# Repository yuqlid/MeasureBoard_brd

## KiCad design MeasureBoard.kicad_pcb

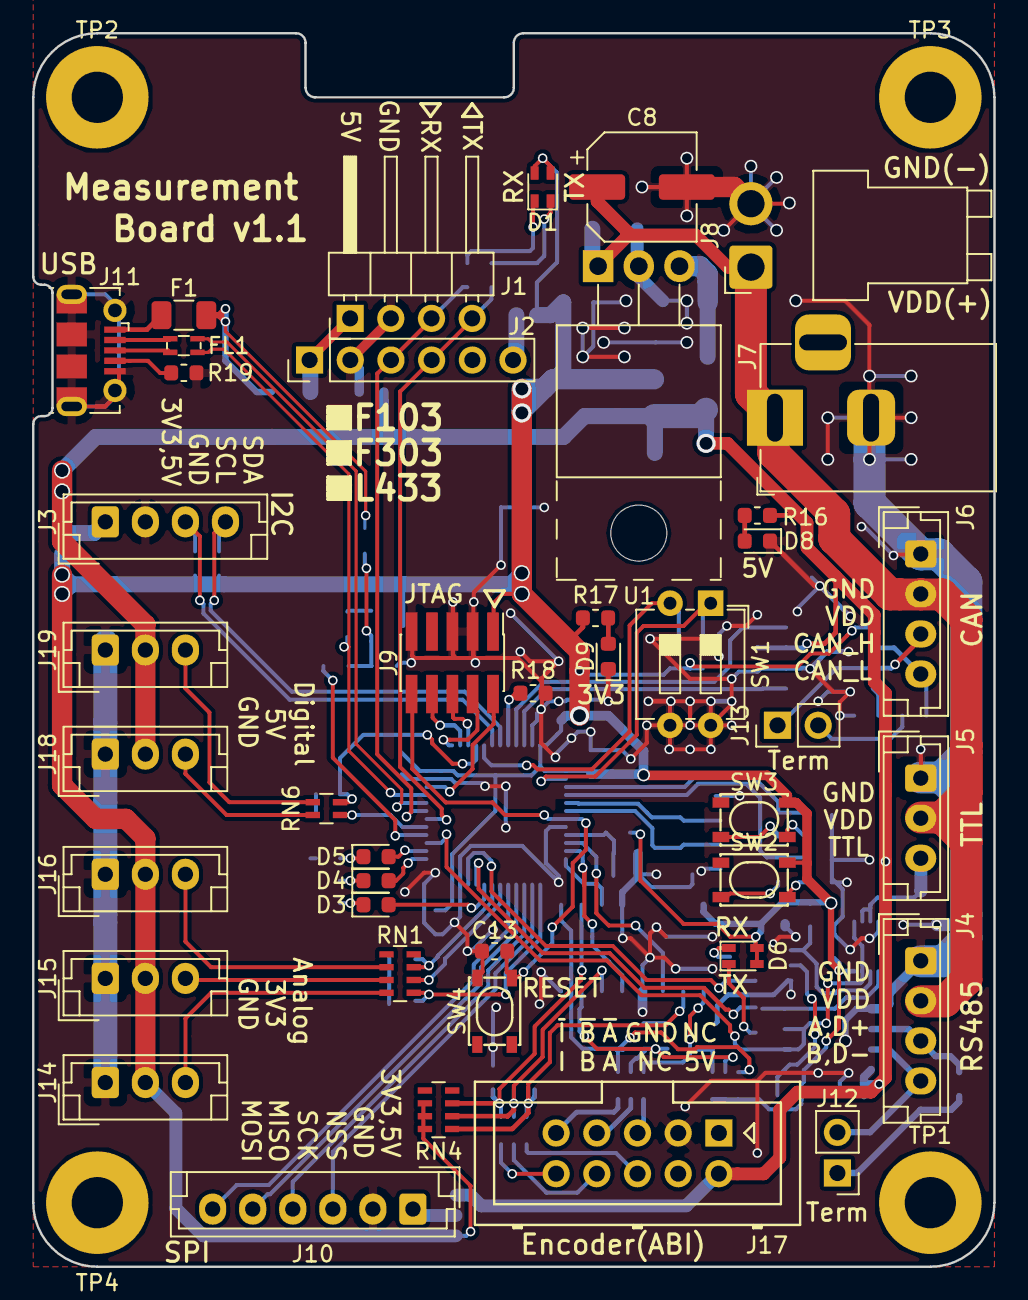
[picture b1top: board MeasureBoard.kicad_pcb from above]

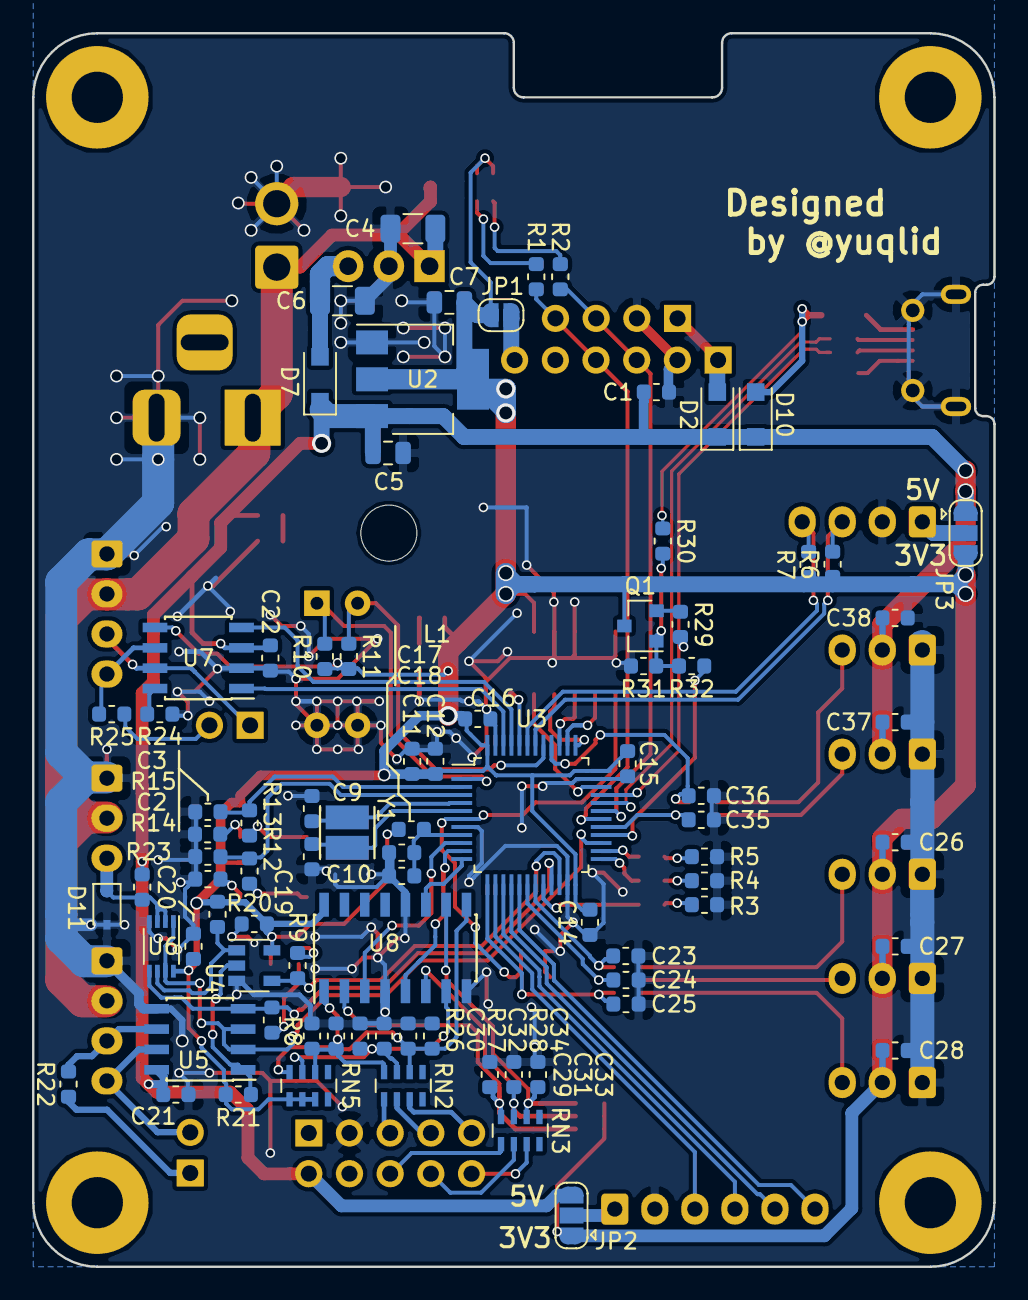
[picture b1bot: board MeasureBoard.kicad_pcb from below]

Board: 2 copper layers, 60.0 x 77.0 mm, 130 parts (84 on the bottom side), 96 nets.

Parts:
C1, C12, C13, C14, C15, C16, C18, C19, C20, C21, C22, C26, C27, C28, C37, C38: 0.1u; C_0603_1608Metric
C2, C3: C; C_0603_1608Metric
C4, C6: C; C_1206_3216Metric
C5, C7: C; C_0805_2012Metric
C8: CP; CP_Elec_6.3x9.9
C9, C10: 14p; C_0603_1608Metric
C11, C17: 1u; C_0603_1608Metric
C23, C24, C25: 1n; C_0603_1608Metric
C29, C30, C31, C32, C33, C34, C35, C36: 220p; C_0603_1608Metric
D1, D6: LED_Dual_ACAC; LED_STANLEY_1211C
D2, D7, D10: D; D_SOD-123F
D3, D4, D5, D8, D9: LED; LED_0603_1608Metric
D11: D_TVS; D_SOD-323
F1: Fuse; Fuse_1206_3216Metric
FL1: EMI_Filter_CommonMode; L_Murata_DLW21HN900SQ2#
J1: Conn_01x04; PinHeader_1x04_P2.54mm_Horizontal
J2: Conn_01x06; PinHeader_1x06_P2.54mm_Vertical
J3, J4, J6: Conn_01x04; JST_EH_B04B-EH-A_1x04_P2.50mm_Vertical
J5, J14, J15, J16, J18, J19: Conn_01x03; JST_EH_B03B-EH-A_1x03_P2.50mm_Vertical
J7: Barrel_Jack_Switch; BarrelJack_Horizontal
J8: Conn_01x02; JST_VH_B2PS-VH_1x02_P3.96mm_Horizontal
J9: Conn_02x05_Odd_Even; PinHeader_2x05_P1.27mm_Vertical_SMD
J10: Conn_01x06; JST_EH_B06B-EH-A_1x06_P2.50mm_Vertical
J11: USB_B_Micro; USB_Micro-B_Molex-105017-0001
J12, J13: Conn_01x02; PinHeader_1x02_P2.54mm_Vertical
J17: Conn_02x05_Odd_Even; Multicomp_MC9A12-1034_2x05_P2.54mm_Vertical
JP1: Jumper_2_Open; SolderJumper-2_P1.3mm_Open_RoundedPad1.0x1.5mm
JP2: SolderJumper_3_Open; SolderJumper-3_P1.3mm_Open_RoundedPad1.0x1.5mm
JP3: Jumper_NC_Dual; SolderJumper-3_P1.3mm_Open_RoundedPad1.0x1.5mm
L1: L; L_0603_1608Metric
Q1: BSS138; SOT-23
R1, R2, R3, R4, R5, R8, R9, R16, R17: 1k; R_0603_1608Metric
R6, R7, R10, R11, R12, R13: 4k7; R_0603_1608Metric
R14, R15, R18, R20, R21, R23, R30: 10k; R_0603_1608Metric
R19, R24, R32: R; R_0603_1608Metric
R22, R25: 120; R_0603_1608Metric
R26, R27, R28: 20k; R_0603_1608Metric
R29: 1.5k; R_0603_1608Metric
R31: 36k; R_0603_1608Metric
RN1, RN2, RN3, RN4, RN5: R_Pack04; R_Array_Concave_4x0603
RN6: R_Pack02; R_Array_Concave_2x0603
SW1: DIP_SW_2P; SW_DIP_SPSTx02_Slide_6.7x6.64mm_W7.62mm_P2.54mm_LowProfile
SW2, SW3, SW4: SKRPACE010; ALPS_SKRPAxE010
TP1, TP2, TP3, TP4: TestPoint; MountingHole_3.2mm_M3_Pad
U1: L7805; TO-220-3_Horizontal_TabUp
U2: AP1117-33; SOT-223-3_TabPin2
U3: STM32F303CCTx; LQFP-48_7x7mm_P0.5mm
U4: NC7SZ08; SOT-23-5
U5: SP3481CN; SOIC-8_3.9x4.9mm_P1.27mm
U6: NC7WZ241; VSSOP-8_2.3x2mm_P0.5mm
U7: MCP2562-E-SN; SOIC-8_3.9x4.9mm_P1.27mm
U8: AM26LV32; SOIC-16_3.9x9.9mm_P1.27mm
Y1: Crystal; NDK_Crystal_SMD_3225_2Pads

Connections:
+3V3: C7.1, C11.2, C12.1, C14.2, C15.2, C16.2, C19.1, C20.1, C26.1, C27.1, C28.1, D1.1, D1.3, D6.1, D6.3, J9.1, J14.2, J15.2, J16.2, JP1.2, JP2.1, JP3.3, L1.1, Q1.3, R6.1, R7.1, R10.1, R11.1, R17.1, R20.1, R21.1, RN4.6, RN4.7, RN4.8, RN5.5, RN5.6, RN5.7, SW2.2, SW3.2, U2.2, U3.1, U3.24, U3.36, U3.48, U4.5, U6.8, U7.5, U8.16
+5V: C1.1, C5.1, C21.1, C22.1, C37.1, C38.1, D2.1, D7.1, D10.1, J17.2, J18.2, J19.2, JP2.3, JP3.1, R16.1, R23.1, U2.3, U5.8, U7.3
+12V: C4.1, C8.1, J4.2, J5.2, J6.2, J7.1, J8.1, U1.1
/CAN/CAN_H: J6.3, J13.1, U7.7
/CAN/CAN_L: J6.4, R25.2, U7.6
/ENCODER/A: U3.10, U8.3
/ENCODER/B: U3.11, U8.5
/ENCODER/I: U3.12, U8.11
/IN_Di/DI1_LPF: C36.1, RN6.2, U3.40
/IN_Di/DI2_LPF: C35.1, RN6.1, U3.29
/JTAG/SWCLK-TCK: J9.4, U3.37
/JTAG/SWDIO-TMS: J9.2, U3.34
/JTAG/SWO-TDO: J9.6, U3.39
/MCU/ADC_IN3: C25.1, RN1.1, U3.13
/MCU/ADC_IN8: C24.1, RN1.2, U3.18
/MCU/ADC_IN9: C23.1, RN1.3, U3.19
/MCU/CAN_RX: U3.45, U7.4
/MCU/CAN_TX: U3.46, U7.1
/MCU/I2C1_SCL: J3.3, R6.2, U3.42
/MCU/I2C1_SDA: J3.4, R7.2, U3.43
/MCU/PB2: D3.2, U3.20
/MCU/PB5: R11.2, SW1.2, U3.41
/MCU/PB12: D4.2, U3.25
/MCU/PB13: D5.2, U3.26
/MCU/PC13: R10.2, SW1.1, U3.2
/MCU/PC14: C3.2, R13.2, U3.3
/MCU/PC15: C2.2, R12.2, U3.4
/MCU/SYS_JTDI: J9.8, U3.38
/MCU/USART1_RX: J1.3, J2.3, R2.1, U3.31
/MCU/USART1_TX: J1.4, J2.4, R1.1, U3.30
/MCU/USART3_RTS: U3.27, U5.2, U5.3, U6.1, U6.7
/RS485-TTL/DI: R8.1, U3.21, U5.4, U6.5
/RS485-TTL/RO: R9.1, U3.22, U4.4
/RS485-TTL/RS485_A: J4.3, R22.2, U5.6
/RS485-TTL/RS485_B: J4.4, J12.2, U5.7
/RS485-TTL/TTL_DATA: D11.1, J5.3, R23.2, U6.2, U6.3
/SSI/DATA_MISO: J10.5, U3.16
/SSI/MOSI: J10.6, U3.17
/SSI/NSS: J10.3, U3.14
/SSI/SCK: J10.4, U3.15
/USB/D+: FL1.4, R29.2, U3.33
/USB/D-: FL1.2, U3.32
/USB/USB_+: FL1.3, J11.3
/USB/USB_-: FL1.1, J11.2
/USB_EN: R32.1, U3.28
GND: C1.2, C2.1, C3.1, C4.2, C5.2, C6.2, C7.2, C8.2, C9.2, C10.2, C11.1, C12.2, C13.2, C14.1, C15.1, C16.1, C17.1, C18.1, C19.2, C20.2, C21.2, C22.2, C23.2, C24.2, C25.2, C26.2, C27.2, C28.2, C29.2, C30.2, C31.2, C32.2, C33.2, C34.2, C35.2, C36.2, C37.2, C38.2, D8.1, D9.1, D11.2, J1.2, J2.2, J3.2, J4.1, J5.1, J6.1, J7.2, J8.2, J9.3, J9.5, J9.9, J10.2, J11.5, J11.6, J14.1, J15.1, J16.1, J17.3, J18.1, J19.1, R3.2, R4.2, R5.2, R14.1, R15.1, R18.2, R19.2, R24.2, R26.2, R27.2, R28.2, R31.2, SW1.3, SW1.4, SW4.2, U1.2, U2.1, U3.8, U3.23, U3.35, U3.47, U4.3, U5.5, U6.4, U7.2, U8.4, U8.8, U8.12
NRST: C13.1, J9.10, SW4.4, U3.7
unnamed: C6.1, D7.2, U1.3
unnamed: C9.1, U3.5, Y1.1
unnamed: C10.1, U3.6, Y1.2
unnamed: C17.2, C18.2, L1.2, U3.9
unnamed: C29.1, RN3.8, RN4.1, U8.2
unnamed: C30.1, R26.1, RN2.8, RN5.2, U8.1
unnamed: C31.1, RN3.7, RN4.2, U8.6
unnamed: C32.1, R27.1, RN2.7, RN5.3, U8.7
unnamed: C33.1, RN3.6, RN4.3, U8.10
unnamed: C34.1, R28.1, RN2.6, RN5.4, U8.9
unnamed: D1.2, R2.2
unnamed: D1.4, R1.2
unnamed: D2.2, J1.1, J2.1
unnamed: D3.1, R3.1
unnamed: D4.1, R4.1
unnamed: D5.1, R5.1
unnamed: D6.2, R9.2
unnamed: D6.4, R8.2
unnamed: D8.2, R16.2
unnamed: D9.2, R17.2
unnamed: D10.2, F1.1, R30.1
unnamed: F1.2, J11.1
unnamed: J2.6, JP1.1
unnamed: J3.1, JP3.2
unnamed: J10.1, JP2.2
unnamed: J11.4, R19.1
unnamed: J12.1, R22.1
unnamed: J13.2, R25.1
unnamed: J14.3, RN1.8
unnamed: J15.3, RN1.7
unnamed: J16.3, RN1.6
unnamed: J17.5, RN2.1
unnamed: J17.6, RN3.1
unnamed: J17.7, RN2.2
unnamed: J17.8, RN3.2
unnamed: J17.9, RN2.3
unnamed: J17.10, RN3.3
unnamed: J18.3, RN6.4
unnamed: J19.3, RN6.3
unnamed: Q1.1, R30.2, R31.1, R32.2
unnamed: Q1.2, R29.1
unnamed: R12.1, SW2.3
unnamed: R13.1, SW3.3
unnamed: R14.2, SW2.4
unnamed: R15.2, SW3.4
unnamed: R18.1, U3.44
unnamed: R20.2, U4.1, U6.6
unnamed: R21.2, U4.2, U5.1
unnamed: R24.1, U7.8

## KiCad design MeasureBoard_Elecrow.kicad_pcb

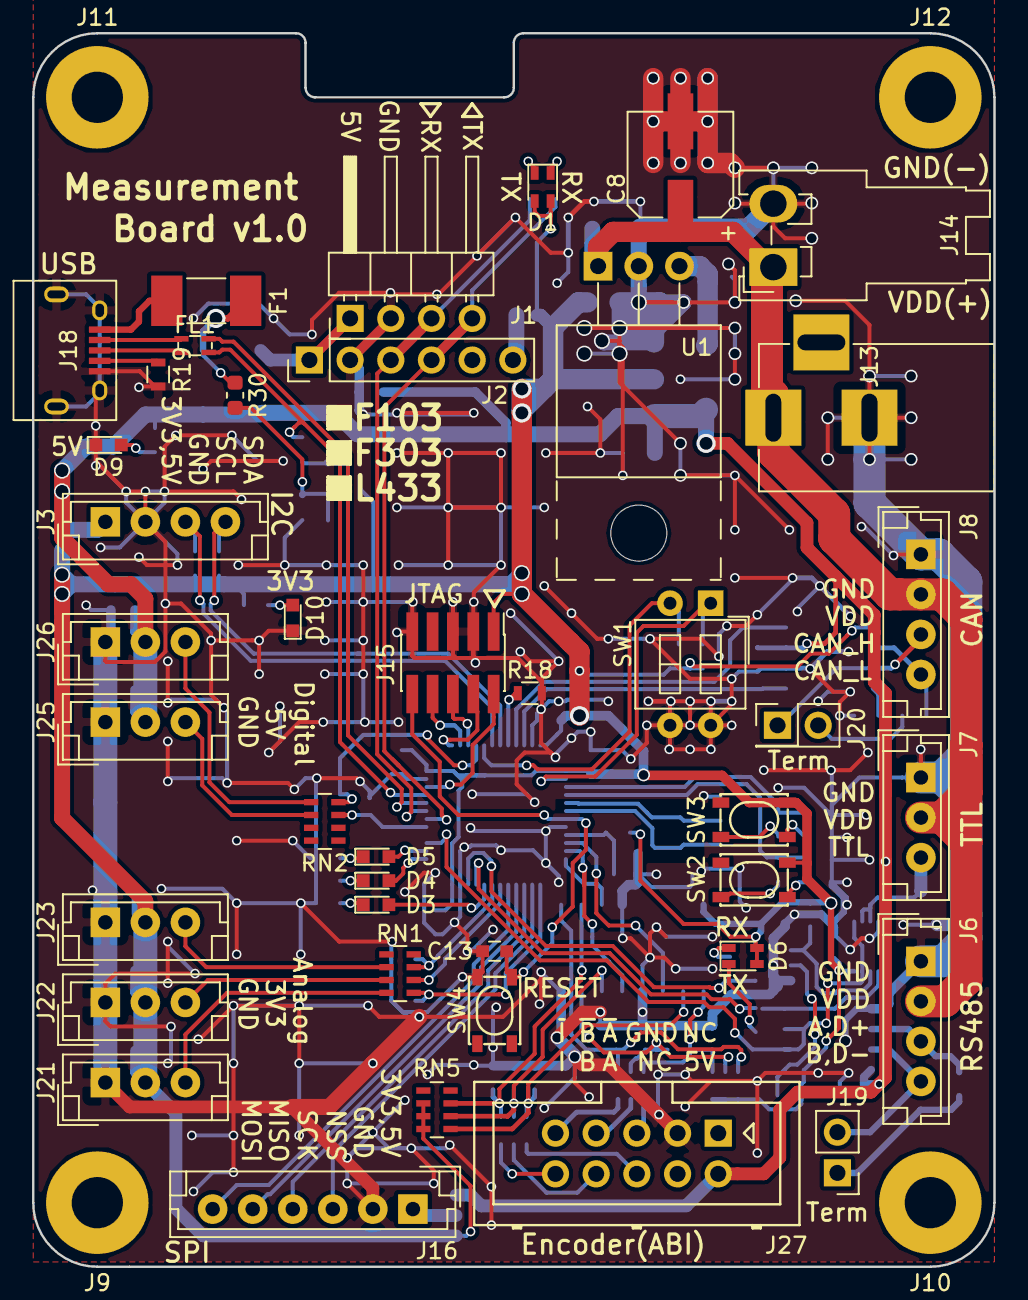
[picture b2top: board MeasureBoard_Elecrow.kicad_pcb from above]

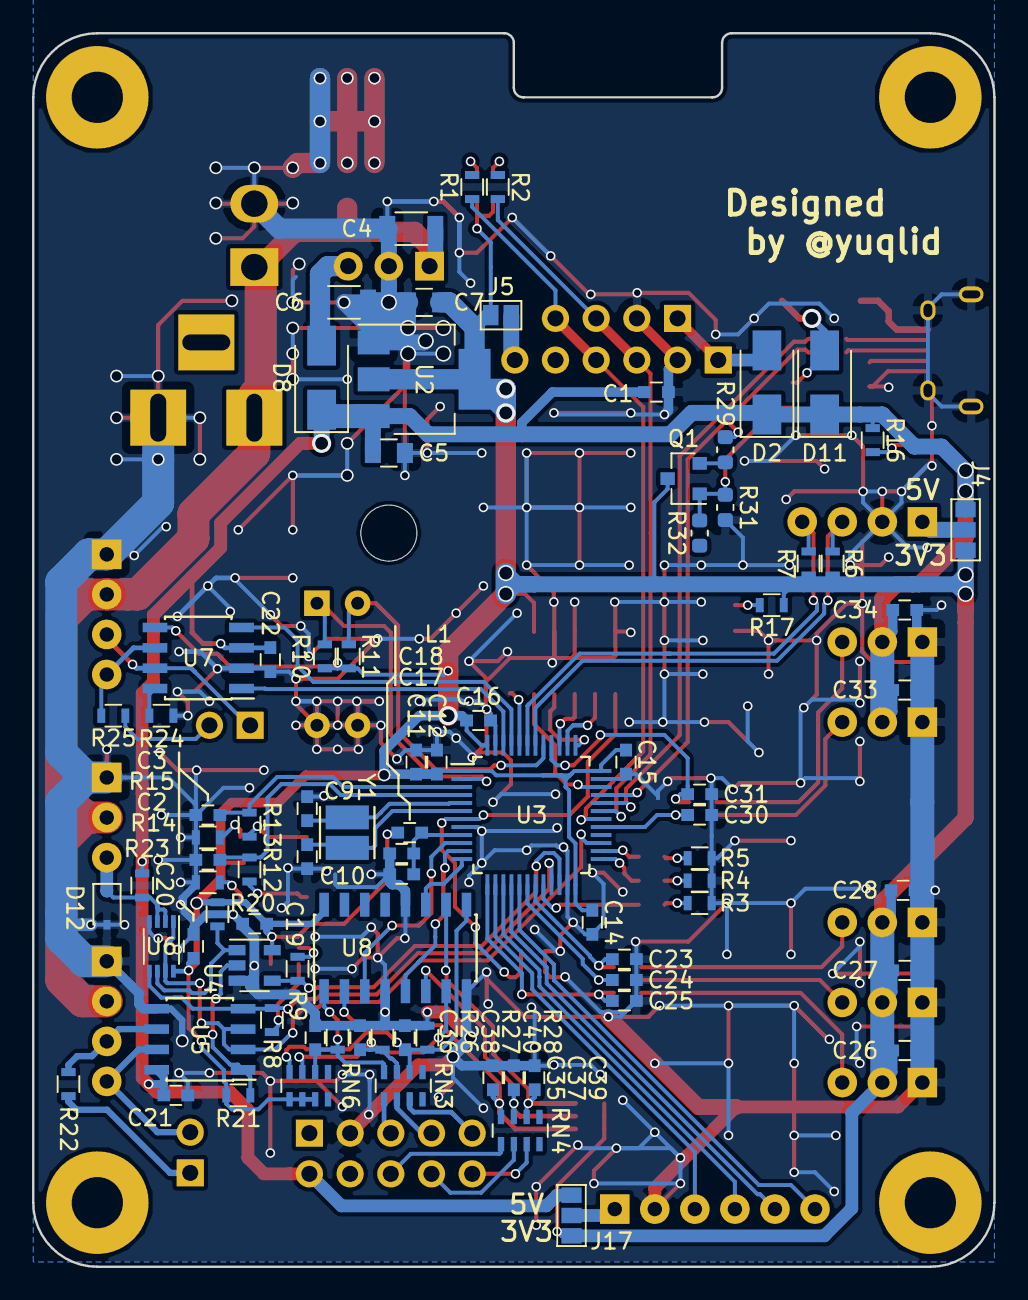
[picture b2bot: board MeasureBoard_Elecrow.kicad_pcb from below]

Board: 2 copper layers, 60.0 x 77.0 mm, 130 parts (85 on the bottom side), 96 nets.

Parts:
C1, C2, C3, C12, C13, C14, C15, C16, C18, C19, C20, C21, C22, C26, C27, C28, C33, C34: 0.1u; C_0603
C4, C6: C; C_1206
C5, C7: C; C_0805
C8: CP; CP_Elec_6.3x7.7
C9, C10: 14p; C_0603
C11, C17: 1u; C_0603
C23, C24, C25: 1n; C_0603
C30, C31, C35, C36, C37, C38, C39, C40: 220p; C_0603
D1, D6: LED_Dual_ACAC; LED_STANLEY_1211C
D2, D8, D11: D; D_SMA
D3, D4, D5, D9, D10: LED; LED_0603
D12: D_TVS; D_SOD-323
F1: Fuse; Fuse_0679H
FL1: EMI_Filter_CommonMode; L_Murata_DLW21HN900SQ2#
J1: Conn_01x04; Pin_Header_Angled_1x04_Pitch2.54mm
J2: Conn_01x06; Pin_Header_Straight_1x06_Pitch2.54mm
J3, J6, J8: Conn_01x04; JST_EH_B04B-EH-A_04x2.50mm_Straight
J4, J17: GS3
J5: GS2
J7, J21, J22, J23, J25, J26: Conn_01x03; JST_EH_B03B-EH-A_03x2.50mm_Straight
J9, J10, J11, J12: TEST_1P; MountingHole_3.2mm_M3_Pad
J13: BARREL_JACK
J14: CONN_01X02; JST_VH_S2P-VH_2x2x3.96mm_Horizontal
J15: Conn_02x05_Odd_Even; Pin_Header_Straight_2x05_Pitch1.27mm_SMD
J16: Conn_01x06; JST_EH_B06B-EH-A_06x2.50mm_Straight
J18: USB_OTG; USB_Micro-B
J19: Conn_01x02; Pin_Header_Straight_1x02_Pitch2.54mm
J20: Conn_01x02; Pin_Header_Straight_2x01_Pitch2.54mm
J27: Conn_02x05_Odd_Even; Multicomp_MC9A12-1034_2x05x2.54mm_Straight
L1: L; C_0603
Q1: BSS138; SOT-23
R1, R2, R3, R4, R5, R8, R9, R16, R17: 1k; R_0603
R6, R7, R10, R11, R12, R13: 4.7k; R_0603
R14, R15, R18, R20, R21, R23: 10k; R_0603
R19: 100k; R_0603
R22, R25: 120; R_0603
R24: R; R_0603
R26, R27, R28: 20k; R_0603
R29: 1.5k; R_0603_1608Metric
R30: 10k; R_0603_1608Metric
R31: 36k; R_0603_1608Metric
R32: R; R_0603_1608Metric
RN1, RN5: 10k_4; R_Array_Concave_4x0603
RN2, RN3, RN4: 150_4; R_Array_Concave_4x0603
RN6: 20k_4; R_Array_Concave_4x0603
SW1: DIP_SW_2P; SW_DIP_x2_W7.62mm_Slide_LowProfile
SW2, SW3, SW4: SKRPACE010; ALPS_SKRPAxE010
U1: L7805; TO-220-3_Horizontal_Reversed
U2: AP1117-33; SOT-223-3_TabPin2
U3: STM32F103CBTx; LQFP-48_7x7mm_Pitch0.5mm
U4: NC7SZ08; SOT-23-5
U5: SP3481CN; SOIC-8_3.9x4.9mm_Pitch1.27mm
U6: NC7WZ241; VSSOP-8_2.3x2mm_Pitch0.5mm
U7: MCP2562-E-SN; SOIC-8_3.9x4.9mm_Pitch1.27mm
U8: AM26LV32; SOIC-16_3.9x9.9mm_Pitch1.27mm
Y1: Crystal; NDK_Crystal_SMD_3225_2Pads

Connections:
+3V3: C7.1, C11.1, C12.1, C14.1, C15.1, C16.1, C19.1, C20.1, C26.1, C27.1, C28.1, D1.1, D1.3, D6.1, D6.3, J4.1, J5.1, J15.1, J17.1, J21.2, J22.2, J23.2, L1.1, Q1.3, R6.1, R7.1, R10.1, R11.1, R17.2, R20.2, R21.2, RN5.6, RN5.7, RN5.8, RN6.5, RN6.6, RN6.7, SW2.2, SW3.2, U2.2, U3.1, U3.24, U3.36, U3.48, U4.5, U6.8, U7.5, U8.16
+5V: C1.1, C5.1, C21.1, C22.1, C33.1, C34.1, D2.1, D8.1, D11.1, J4.3, J17.3, J25.2, J26.2, J27.2, R16.2, R23.2, U2.3, U5.8, U7.3
+12V: C4.1, C8.1, J6.2, J7.2, J8.2, J13.1, J14.1, U1.1
/CAN/CAN_H: J8.3, J20.1, U7.7
/CAN/CAN_L: J8.4, R25.1, U7.6
/ENCODER/A: U3.10, U8.3
/ENCODER/B: U3.11, U8.5
/ENCODER/I: U3.12, U8.11
/IN_Di/DI1_LPF: C31.1, RN2.4, U3.40
/IN_Di/DI2_LPF: C30.1, RN2.3, U3.29
/JTAG/SWCLK-TCK: J15.4, U3.37
/JTAG/SWDIO-TMS: J15.2, U3.34
/JTAG/SWO-TDO: J15.6, U3.39
/MCU/ADC_IN3: C25.1, RN1.1, U3.13
/MCU/ADC_IN8: C24.1, RN1.2, U3.18
/MCU/ADC_IN9: C23.1, RN1.3, U3.19
/MCU/CAN_RX: U3.45, U7.4
/MCU/CAN_TX: U3.46, U7.1
/MCU/I2C1_SCL: J3.3, R6.2, U3.42
/MCU/I2C1_SDA: J3.4, R7.2, U3.43
/MCU/PB2: D3.2, U3.20
/MCU/PB5: R11.2, SW1.2, U3.41
/MCU/PB12: D4.2, U3.25
/MCU/PB13: D5.2, U3.26
/MCU/PC13: R10.2, SW1.1, U3.2
/MCU/PC14: C3.2, R13.2, U3.3
/MCU/PC15: C2.2, R12.2, U3.4
/MCU/SYS_JTDI: J15.8, U3.38
/MCU/USART1_RX: J1.3, J2.3, R2.1, U3.31
/MCU/USART1_TX: J1.4, J2.4, R1.1, U3.30
/MCU/USART3_RTS: U3.27, U5.2, U5.3, U6.1, U6.7
/RS485-TTL/DI: R8.2, U3.21, U5.4, U6.5
/RS485-TTL/RO: R9.2, U3.22, U4.4
/RS485-TTL/RS485_A: J6.3, R22.1, U5.6
/RS485-TTL/RS485_B: J6.4, J19.2, U5.7
/RS485-TTL/TTL_DATA: D12.1, J7.3, R23.1, U6.2, U6.3
/SSI/DATA_MISO: J16.5, U3.16
/SSI/MOSI: J16.6, U3.17
/SSI/NSS: J16.3, U3.14
/SSI/SCK: J16.4, U3.15
/USB/D+: FL1.4, R29.2, U3.33
/USB/D-: FL1.2, U3.32
/USB/USB_+: FL1.3, J18.3
/USB/USB_-: FL1.1, J18.2
/USB_EN: R32.1, U3.28
GND: C1.2, C2.1, C3.1, C4.2, C5.2, C6.2, C7.2, C8.2, C9.1, C10.1, C11.2, C12.2, C13.2, C14.2, C15.2, C16.2, C17.1, C18.1, C19.2, C20.2, C21.2, C22.2, C23.2, C24.2, C25.2, C26.2, C27.2, C28.2, C30.2, C31.2, C33.2, C34.2, C35.2, C36.2, C37.2, C38.2, C39.2, C40.2, D9.1, D10.1, D12.2, J1.2, J2.2, J3.2, J6.1, J7.1, J8.1, J13.2, J14.2, J15.3, J15.5, J15.9, J16.2, J18.5, J18.6, J21.1, J22.1, J23.1, J25.1, J26.1, J27.3, R3.1, R4.1, R5.1, R14.1, R15.1, R18.2, R19.2, R24.1, R26.2, R27.2, R28.2, R31.2, SW1.3, SW1.4, SW4.2, U1.2, U2.1, U3.8, U3.23, U3.35, U3.47, U4.3, U5.5, U6.4, U7.2, U8.4, U8.8, U8.12
NRST: C13.1, J15.10, SW4.4, U3.7
unnamed: C6.1, D8.2, U1.3
unnamed: C9.2, U3.5, Y1.1
unnamed: C10.2, U3.6, Y1.2
unnamed: C17.2, C18.2, L1.2, U3.9
unnamed: C35.1, RN4.8, RN5.1, U8.2
unnamed: C36.1, R26.1, RN3.8, RN6.2, U8.1
unnamed: C37.1, RN4.7, RN5.2, U8.6
unnamed: C38.1, R27.1, RN3.7, RN6.3, U8.7
unnamed: C39.1, RN4.6, RN5.3, U8.10
unnamed: C40.1, R28.1, RN3.6, RN6.4, U8.9
unnamed: D1.2, R2.2
unnamed: D1.4, R1.2
unnamed: D2.2, J1.1, J2.1
unnamed: D3.1, R3.2
unnamed: D4.1, R4.2
unnamed: D5.1, R5.2
unnamed: D6.2, R9.1
unnamed: D6.4, R8.1
unnamed: D9.2, R16.1
unnamed: D10.2, R17.1
unnamed: D11.2, F1.1, R30.1
unnamed: F1.2, J18.1
unnamed: J2.6, J5.2
unnamed: J3.1, J4.2
unnamed: J16.1, J17.2
unnamed: J18.4, R19.1
unnamed: J19.1, R22.2
unnamed: J20.2, R25.2
unnamed: J21.3, RN1.8
unnamed: J22.3, RN1.7
unnamed: J23.3, RN1.6
unnamed: J25.3, RN2.6
unnamed: J26.3, RN2.5
unnamed: J27.5, RN3.1
unnamed: J27.6, RN4.1
unnamed: J27.7, RN3.2
unnamed: J27.8, RN4.2
unnamed: J27.9, RN3.3
unnamed: J27.10, RN4.3
unnamed: Q1.1, R30.2, R31.1, R32.2
unnamed: Q1.2, R29.1
unnamed: R12.1, SW2.3
unnamed: R13.1, SW3.3
unnamed: R14.2, SW2.4
unnamed: R15.2, SW3.4
unnamed: R18.1, U3.44
unnamed: R20.1, U4.1, U6.6
unnamed: R21.1, U4.2, U5.1
unnamed: R24.2, U7.8

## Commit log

2018-05-15 プロジェクト追加
2018-05-15 MCUのピンを引き出した
2018-05-15 各インターフェースの図面追加
2018-05-15 引けるぶんひいた
2018-05-17 バックアップ
2018-05-17 upadte
2018-05-18 AW進捗
2018-05-18 UARTにLED追加
2018-05-23 gndのパスを修正
2018-05-23 一回区切りついた
2018-05-24 udpate
2018-05-24 コモンモードフィルタつけた
2018-05-25 再アノテーション，電解コンデンサ追加
2018-06-13 シルク修正
2018-06-14 USBのいち変更
2018-08-01 KiCadのバージョンを5.0にアップデート USART3のLEDを調整
2018-08-02 USBのDPのプルアップ抵抗をフローティングにする回路追加
2018-12-19 USB，D+周りの変更をAWにまで適用した．
2019-02-20 ??のシンボルを戻した，疲れた
2019-02-21 アノテーションしたけど部品配置がパーになって萎えた
2019-03-02 DRCパス
2019-03-03 ちびちび修正
